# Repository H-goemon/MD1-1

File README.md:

# MD1-1 (110番モタドラ)
## 仕様
・DCモーターを一つ、動かせます

・耐圧、ノイズ耐性ともに個体差あり，私の気まぐれで部品がくっついていない場合がある.

・三端子レギュレータを介さずに，駆動電源から信号電源を取れるようにするジャンパあり．

## 部品詳細仕様

| 部品  | 型番 | 内容 |
| ------------- | ------------- | ------------- |
| MOSFET  | 不明  |   |
| ゲートドライバ  | IR2104  |  耐圧25V，MOSFETに与える処理をできる |
| フォトカプラ | TLP152 | 耐圧30V，絶縁しつつ，マイコンの信号と信号を分ける |
| 三端子レギュレータ | 7812? | 電源電圧から12V信号電圧へ降圧するために使用．一年生教育ではもったいないので外している． |

リポバッテリーを用いる際は三端子レギュレータを使って信号電圧を降圧させること．

（4セルので，耐圧にギリギリ耐えるくらいなので潔く三端子レギュレータを用いるほうが無難）

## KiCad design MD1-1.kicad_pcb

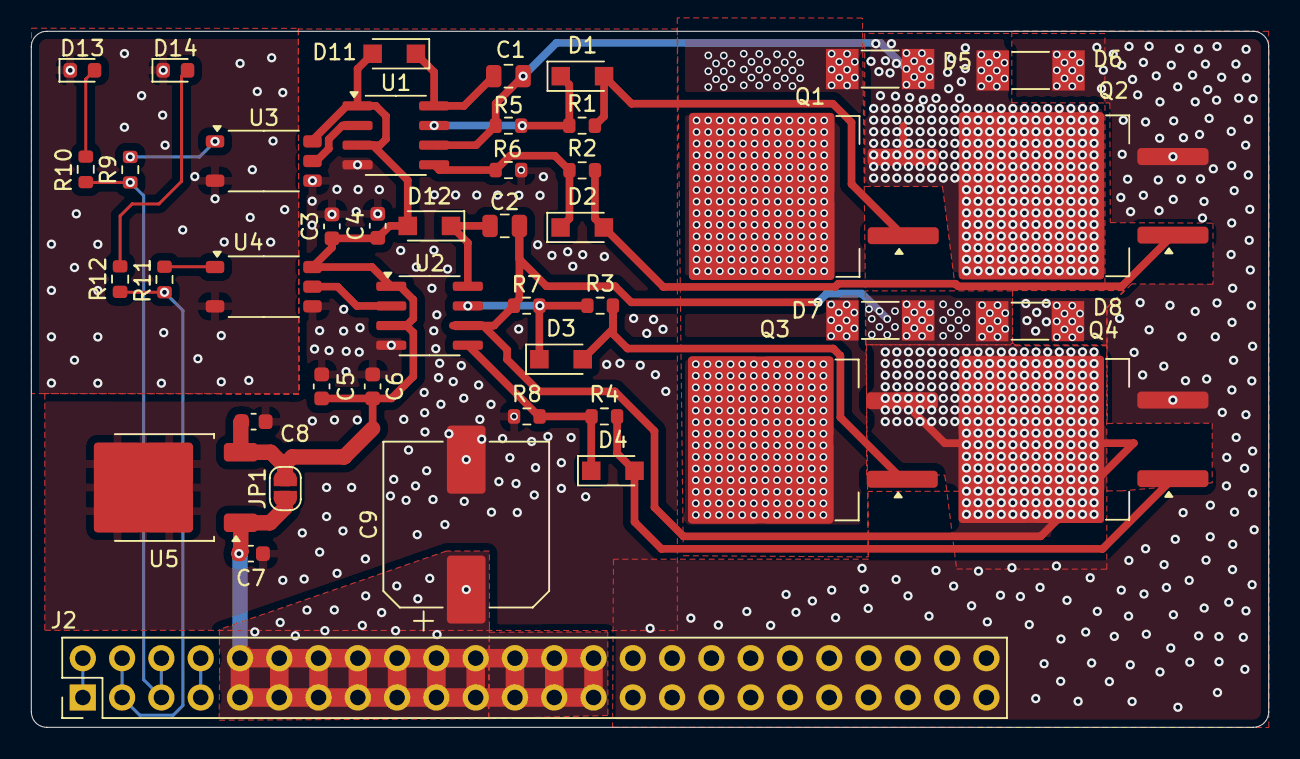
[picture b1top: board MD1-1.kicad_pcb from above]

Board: 2 copper layers, 80.0 x 45.0 mm, 44 parts (0 on the bottom side), 25 nets.

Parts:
C1, C2: 10μF; C_0805_2012Metric
C3, C4, C5, C6, C8: 0.1μF; C_0603_1608Metric
C7: 0.33μF; C_0603_1608Metric
C9: 47μF; CP_Elec_10x10.5
D1, D2, D3, D4, D11: 1N4148W; Nexperia_CFP3_SOD-123W
D5, D6, D7, D8: 1N4148W; R_MELF_MMB-0207
D12: D; Nexperia_CFP3_SOD-123W
D13, D14: LED; LED_0603_1608Metric
J2: Conn_02x24_Counter_Clockwise; PinHeader_2x24_P2.54mm_Vertical
JP1: 24V⇔12V切り替え; SolderJumper-2_P1.3mm_Open_RoundedPad1.0x1.5mm
Q1, Q2, Q3, Q4: NMOS; TO-263-2
R1, R2, R3, R4: 10Ω; R_0603_1608Metric
R5, R6, R7, R8: 10kΩ; R_0603_1608Metric
R9, R10, R11, R12: 1kΩ; R_0603_1608Metric
U1, U2: IR2302; SOIC-8_3.9x4.9mm_P1.27mm
U3, U4: TLP152; SO-5-6_4.55x3.7mm_P1.27mm
U5: L7812; TO-252-2

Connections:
+3.3V: J2.1, J2.48
+12V: C3.1, C4.1, C5.1, C6.1, C8.1, D11.2 (A), D12.2 (A), JP1.2 (B), U1.1 (VCC), U1.3 (~SD), U2.1 (VCC), U2.3 (~SD), U3.6, U4.6, U5.3 (OUT)
+Batt: C7.1, C9.1, D5.1 (K), D7.1 (K), J2.5, J2.6, J2.7, J2.8, J2.9, J2.10, J2.11, J2.12, J2.13, J2.14, J2.35, J2.36, J2.37, J2.38, J2.39, J2.40, J2.41, J2.42, J2.43, J2.44, JP1.1 (A), Q1.1 (D), Q3.1 (D), U5.1 (IN)
/MD1-1_Card1/Foward-Sig: J2.3, J2.46, R9.1, R10.1
/MD1-1_Card1/Rear-Sig: J2.2, J2.47, R11.2, R12.1
GND: C3.2, C4.2, C5.2, C6.2, C7.2, C8.2, C9.2, D6.2 (A), D8.2 (A), J2.15, J2.16, J2.17, J2.18, J2.19, J2.20, J2.21, J2.22, J2.23, J2.24, J2.25, J2.26, J2.27, J2.28, J2.29, J2.30, J2.31, J2.32, J2.33, J2.34, Q2.3 (S), Q4.3 (S), R6.2, R8.2, U1.4 (COM), U2.4 (COM), U3.4, U4.4, U5.2 (GND)
GNDSig: D13.1 (K), D14.1 (K), J2.4, J2.45, U3.3, U4.3
unnamed: D1.2 (A), Q1.2 (G), R1.2
unnamed: D1.1 (K), R1.1, R5.1, U1.7 (HO)
unnamed: D2.2 (A), Q2.2 (G), R2.2
unnamed: D2.1 (K), R2.1, R6.1, U1.5 (LO)
unnamed: D3.2 (A), Q3.2 (G), R3.2
unnamed: D3.1 (K), R3.1, R7.1, U2.7 (HO)
unnamed: D4.2 (A), Q4.2 (G), R4.2
unnamed: D4.1 (K), R4.1, R8.1, U2.5 (LO)
unnamed: C1.1, D11.1 (K), U1.8 (VB)
unnamed: C2.1, D12.1 (K), U2.8 (VB)
unnamed: D13.2 (A), R10.2
unnamed: D14.2 (A), R12.2
unnamed: R9.2, U3.1
unnamed: R11.1, U4.1
unnamed: U1.2 (IN), U3.5
unnamed: U2.2 (IN), U4.5
OutA: C1.2, D5.2 (A), D6.1 (K), Q1.3 (S), Q2.1 (D), R5.2, U1.6 (VS)
OutB: C2.2, D7.2 (A), D8.1 (K), Q3.3 (S), Q4.1 (D), R7.2, U2.6 (VS)
